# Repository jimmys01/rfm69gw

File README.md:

# RFM69GW

This is a RFM69 gateway for an ESP8266-based custom board.

The project is currently in beta-stage with a working hardware prototype and full featured code. Both the code, libraries and eagle schematics and board layout are free and open source and can be found in this repository.

## Hardware

The custom PCB has the minimum required components:

* ESP12 footprint
* RFM69CW module footprint
* Two push buttons to RESET and FLASH the board
* A 2.1 5mm jack for powering with AMS1117-3V3 to power the modules
* Filtering and push  up resistors and capacitors
* A 5 pin header to program it
* An edge footprint for an SMA or RP-SMA antenna

The ESP12 and RFM69CW modules are wired according to the following schema:

| ESP12  | NodeMCU | RFM69CW |
|--------|---------|---------|
| GPIO5  | D1      | DIO0    |
| GPIO12 | D6      | MISO    |
| GPIO13 | D7      | MOSI    |
| GPIO14 | D5      | SCK     |
| GPIO15 | D8      | NSS     |
| GPIO16 | D0      | RST     |

Note: there was an error in the ESP12 footprint for version 0.1 of the board: GPIO 4 and 5 were swapped. The schematic showed the IRQ pin to be GPIO4, but the GPIO5 pin was the pin in use.

You can also use your own hardware, SPI pins will probably be the same, only remember to change the pin numbers for SPI_CS and interruption in the RFM69Manager.h file.

```
#define SPI_CS              SS   // GPIO15 (D8)
#define IRQ_PIN             5    // GPIO5  (D1)
#define USE_RESET_PIN       true // Only if RFM's RESET pin connected.
#define RESET_PIN           16   // GPIO16 (D0)
```

## Firmware

* **WebServer for configuration** using the great [PureCSS framework][1]
* **Flashing firmware Over-The-Air** (OTA)
* Up to **3 configurable WIFI networks**
* **MQTT support**
* Arbitrary number of **mappings between nodes/keys and MQTT topics** (as long as there is free memory available)
* Optional default topic for non mapped nodes/keys.
* Configurable IP and Heartbeat topics
* Visual status of the received messages via the ESP12 LED

The project uses a series of state-of-the-art libraries:

* [RFM69_ATC][5] by Felix Rusu and Thomas Studwell with a small change (check patch above)
* [PubSubClient][3] by Nick O'Leary
* [ArduinoJson][4] by Benoit Blanchon
* [Embedis][7] by PatternAgents
* [PureCSS][1] by Yahoo
* And some of the libraries from the [Arduino core for ESP8266][10], by @igrr (Ivan Grokhotkov), @Links2004, @me-no-dev et a,.

## Flashing

The board has a header with 3V3, GND, RX and TX pins, and two buttons for RESET and FLASH. Connect the pins to your favorite FTDI-like programmer. Remember: **only 3V3 voltage** and connect RX to your FTDI TX pin and TX to your RX pin.

To enter flash mode you have to hold the FLASH button pressed while reseting the board with the RESET button.

The project is ready to be build using [PlatformIO][2].
Please refer to their web page for instructions on how to install the builder. Once installed:

```bash
> platformio run --target upload -e wire
> platformio run --target uploadfs -e wire
```

Once you have flashed it you can flash it again over-the-air using the ```ota``` environment:

```bash
> platformio run --target upload -e ota
> platformio run --target uploadfs -e ota
```

When using OTA environment it defaults to the IP address of the device in SoftAP mode. If you want to flash it when connected to your home network best way is to supply the IP of the device:

```bash
> platformio run --target upload -e ota --upload-port 192.168.1.151
> platformio run --target uploadfs -e ota  --upload-port 192.168.1.151
```

Library dependencies not included in the project are automatically managed via PlatformIO Library Manager.

## Usage

On normal boot (i.e. button not pressed) it will execute the firmware. It configures the radio, the SPIFFS memory access, the WIFI, the WebServer and MQTT connection.

Obviously the default values for WIFI network and MQTT will probably not match your requirements. The device will start in Soft AP creating a WIFI SSID named "RFM69_GATEWAY". Connect with phone, PC, laptop, whatever to that network, password is "fibonacci". Once connected browse to 192.168.4.1 and you will be presented a configuration page where you will be able to define up to 3 possible WIFI networks and the MQTT configuration parameters, and topic mappings.

It will then try to connect to the configured WIFI networks one after the other. If none of the 3 attempts succeed it will default to SoftAP mode again. Once connected it will try to connect the MQTT server.

You can configure several aspects, most importantly:

* up to 3 **wifi SSID and password**
* **MQTT server, port** and optionally **user and password**
* **MQTT topics for IP and heartbeat messages**
* **nodeID**, **key** and **topic** to map a given key from a given nodeID to a certain MQTT topic
* a **defaultTopic**, if defined, will be used as a default topic for any combination of nodeID+key not mapped. You can use {nodeid} and {key} as placeholders that will be replaced in execution time.

Messages from the nodes (probably Monteinos) do have to stick to one of these formats:

```
<key>:<value>
<key>:<value>:<packetID>
```

The first one being the default for Rusu's MotionNotes, for instance. "BAT:3812" could be a valid payload to notify battery status. The ```send``` method of the RFM69Manager library included will take care of the formatting. It will also add a correlative packetID that will be used in the gateway to detect duplicates or missing packages.

The RFM69Manager library inherits from RFM69_ATC, so it supports [Automatic Transmission Control][8] that improves battery life by reducing radio power dynamically.

The device will publish its IP to the given topic upon reboot and will send a heartbeat message every 60 seconds.

## Troubleshooting

After flashing the firmware via serial do a hard reset of the device (unplug & plug). There is an issue with the ESP.reset() method that may stuck the device after an OTA update. Check [https://github.com/esp8266/Arduino/issues/1017][3] for more info.

[1]: http://purecss.io/
[2]: http://www.platformio.org
[3]: https://github.com/knolleary/pubsubclient
[4]: https://github.com/bblanchon/ArduinoJson
[5]: https://github.com/LowPowerLab/RFM69
[6]: https://github.com/LowPowerLab/SPIFlash
[7]: https://github.com/thingSoC/embedis
[8]: https://lowpowerlab.com/blog/2015/11/11/rfm69_atc-automatic-transmission-control/
[9]: https://github.com/xoseperez/SPIFlash
[10]: https://github.com/esp8266/Arduino

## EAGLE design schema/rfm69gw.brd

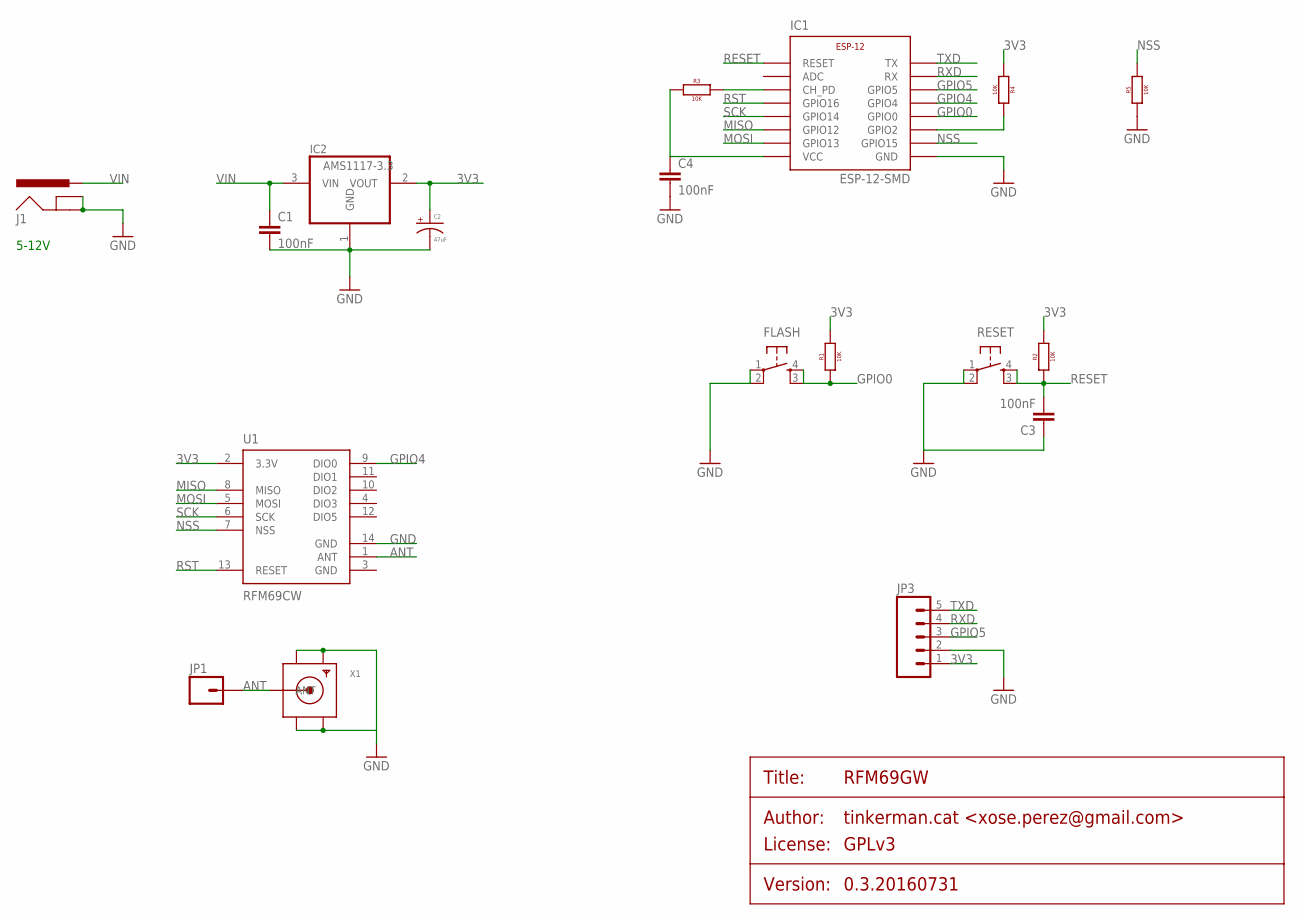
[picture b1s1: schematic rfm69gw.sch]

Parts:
C1, C3, C4: 100nF; C050-025X075
C2: 47uF; CPOL-RADIAL-10UF-25V
FLASH: TACTILE_BUTTON_SMD; TACTILE-BUTTON-SMD
IC1: ESP-12-SMD
IC2: AMS1117-3.3; SOT223
J1: POWER_JACKPTH; POWER_JACK_PTH
JP1: M01SMDNS; 1X01NS
JP3: M05PTH; 1X05
R1, R2, R3, R4, R5: 10K; AXIAL-0.4
RESET: TACTILE_BUTTON_SMD; TACTILE-BUTTON-SMD
U1: RFM69CW; RFM69CW-XXXS2
X1: SMACONNECTOR_EDGE; SMA_EDGELAUNCH

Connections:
3V3: C2.1 (+), C4.1, IC1.VCC, IC2.2 (VOUT), JP3.1, R1.P$2 (2), R2.P$2 (2), R3.P$1 (1), R4.P$1 (1), U1.2 (3.3V)
ANT: JP1.1, U1.1 (ANT), X1.P (ANT)
GND: C1.2, C2.2 (-), C3.1, C4.2, FLASH.1 (SWA1), FLASH.2 (SWB1), IC1.GND, IC2.1 (GND), J1.GND, J1.GNDBREAK, JP3.2, R5.P$1 (1), RESET.1 (SWA1), RESET.2 (SWB1), U1.3 (GND), U1.14 (GND), X1.GND@1 (GND4), X1.GND@2 (GND3), X1.GND@3 (GND2), X1.GND@4 (GND1)
GPIO0: FLASH.3 (SWB2), FLASH.4 (SWA2), IC1.GPIO0, R1.P$1 (1)
GPIO4: IC1.GPIO4, U1.9 (DIO0)
GPIO5: IC1.GPIO5, JP3.3
MISO: IC1.GPIO12, U1.8 (MISO)
MOSI: IC1.GPIO13, U1.5 (MOSI)
unnamed: IC1.CH_PD, R3.P$2 (2)
unnamed: IC1.GPIO2, R4.P$2 (2)
NSS: IC1.GPIO15, R5.P$2 (2), U1.7 (NSS)
RESET: C3.2, IC1.RESET, R2.P$1 (1), RESET.3 (SWB2), RESET.4 (SWA2)
RST: IC1.GPIO16, U1.13 (RESET)
RXD: IC1.RX, JP3.4
SCK: IC1.GPIO14, U1.6 (SCK)
TXD: IC1.TX, JP3.5
VIN: C1.1, IC2.3 (VIN), J1.PWR

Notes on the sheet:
5-12V

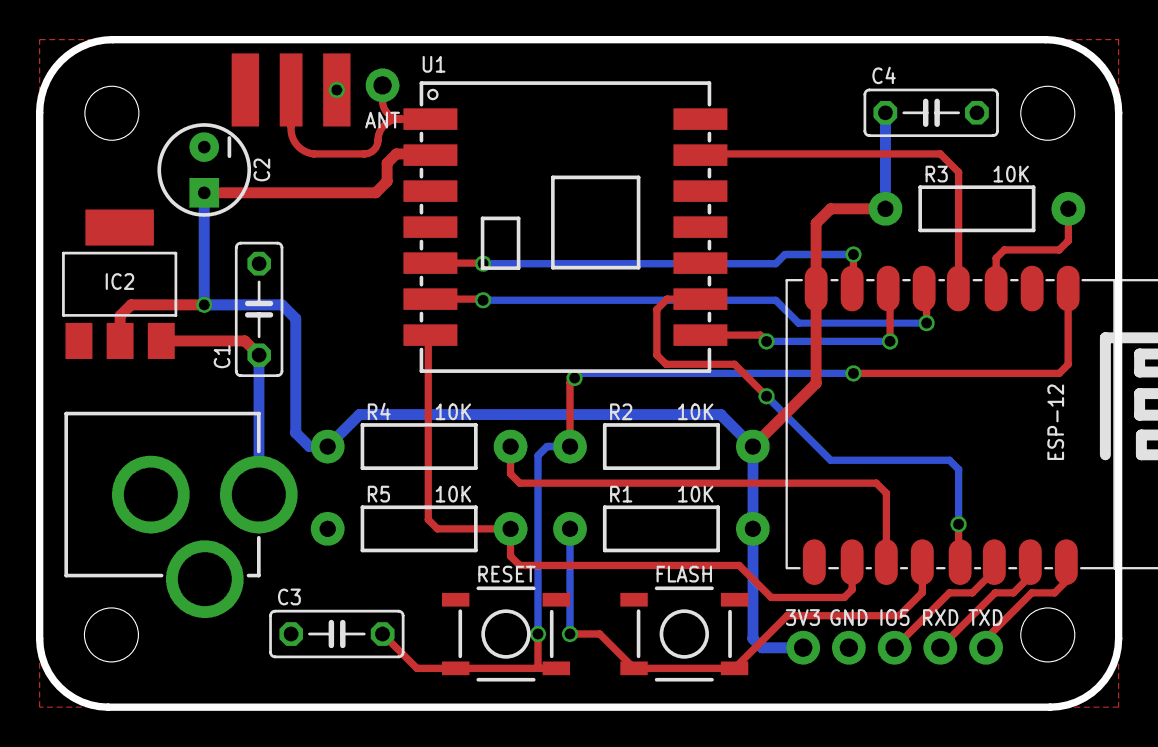
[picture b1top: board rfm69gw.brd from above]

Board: 2 copper layers, 59.9 x 37.1 mm, 18 parts (0 on the bottom side), 17 nets.

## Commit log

2016-08-18 Readme and license files
2016-08-18 Added images to README file
2016-08-18 Board images
2016-08-19 Small fixes, linked modified SPIFlash library as submodule
2016-08-19 Fix some wrong comment sin README file
2016-08-25 Tunned RFM69 for ESP8266 and folder refactor
2016-08-25 Update README with new modifications required by the RFM69 library
2016-08-27 Option to disable packetID in messages + small changes
2016-08-28 Wifi reconnect after X miniutes if in AP mode, valid credentials and no webclient present
2016-08-28 Added option to autocommit configuration changes to EEPROM, changed entry points
2016-08-28 Reconnect from MQTT broker when MQTT configuration changes but WIFI does not
2016-08-28 Save settings only if they have changed
2016-08-28 Small changes in web interface
2016-08-29 Using digitalPinToInterrupt instead of hardcoded IRQ nums
2016-09-29 Update platformio.ini to version 3
2016-10-03 Updated JustWifi library, updated web interface, added promiscuous mode support
2016-10-03 Schema updated
2016-10-07 Imported changes from ESPurna
2016-10-07 Refactor platformio.ini file
2016-10-16 s/monteino/moteino
2016-10-16 Better support for promiscuous mode in RFM69Manager
2016-10-21 Using officially suported platformio.ini file
2016-12-02 Using async libraries, changed AJAX queries wit WebSockets,...
2016-12-02 Added messages tab on web interface
2016-12-04 Added reverse filtering and clear filters button
2016-12-04 Using JustWifi library from PlatformIO libmanager :)
2017-01-02 Allow multi-packet websocket frames
2017-01-02 Gateway version bump
2017-01-22 Issue #2. Set max packet length in RFMManager::send to RF69_MAX_DATA_LEN
2017-01-22 Issue #2. Allow user to define packet separator, defaults to :
2017-01-22 Update changelog
2017-02-06 Reconnect to wifi after MQTT_MAX_TRIES
2017-02-14 Version 0.9.4
2017-10-30 Small changes in the gateway layout
2017-10-31 Whola lotta changes
2017-10-31 Fix & clean web UI
2017-10-31 Fixing WS and MQTT for messages
2017-10-31 Small changes in webUI
2017-10-31 Report uptime & free heap to ws clients on heartbeat
2017-10-31 Fix ESPAsyncTCP dependency for 2.3.0
2017-11-13 Set heartbeat period to 60 seconds, reduce messages
2017-11-13 Show user friendly uptime in webui
2018-01-11 Version 1.0.1
2018-02-05 Fix reference to RFM69 library version
2018-02-05 Fix unmet dependency (#6)
2018-06-11 Fix justwifi reference in platformio.ini
2019-04-16 Pin ArduinoJson library to 5.6
    The API changed in 6+ and the project doesn't even
    compile with those current versions, so instead pin
    to the last the previous major version line.
2019-04-27 Update README for current code (and document NodeMCU)
    I worked through getting the project up and running on own hardware and
    came across a couple of discrepancies between the current codebase and
    the documentation:
    - Pin GPIO4 was listed to connect to RFM69 pin DIO0 (like the bug in the
    schematic), but the code defines pin GPIO5.
    - Lists a required patch to RFM69.cpp to change the SPI clock divider,
2019-04-27 Implement RFH69 hardware reset at boot.
    The ESP module's GPIO16 and the RFM module's RST pin are already
    connected in the schematic and PCB design. However this connection
    wasn't documented in the README, and doesn't appear to be used in the
    software that I can tell.
    In my personal testing (with a NodeMCU) I was originall unable to get
    the radio to receive data. In my debugging I noticed another similar

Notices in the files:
schema/rfm69gw.sch:
PROJECT_LICENSE: GPLv3
parts and their libraries:
SparkFun-Connectors: Licensing: Creative Commons ShareAlike 4.0 International - https://creativecommons.org/licenses/by-sa/4.0
